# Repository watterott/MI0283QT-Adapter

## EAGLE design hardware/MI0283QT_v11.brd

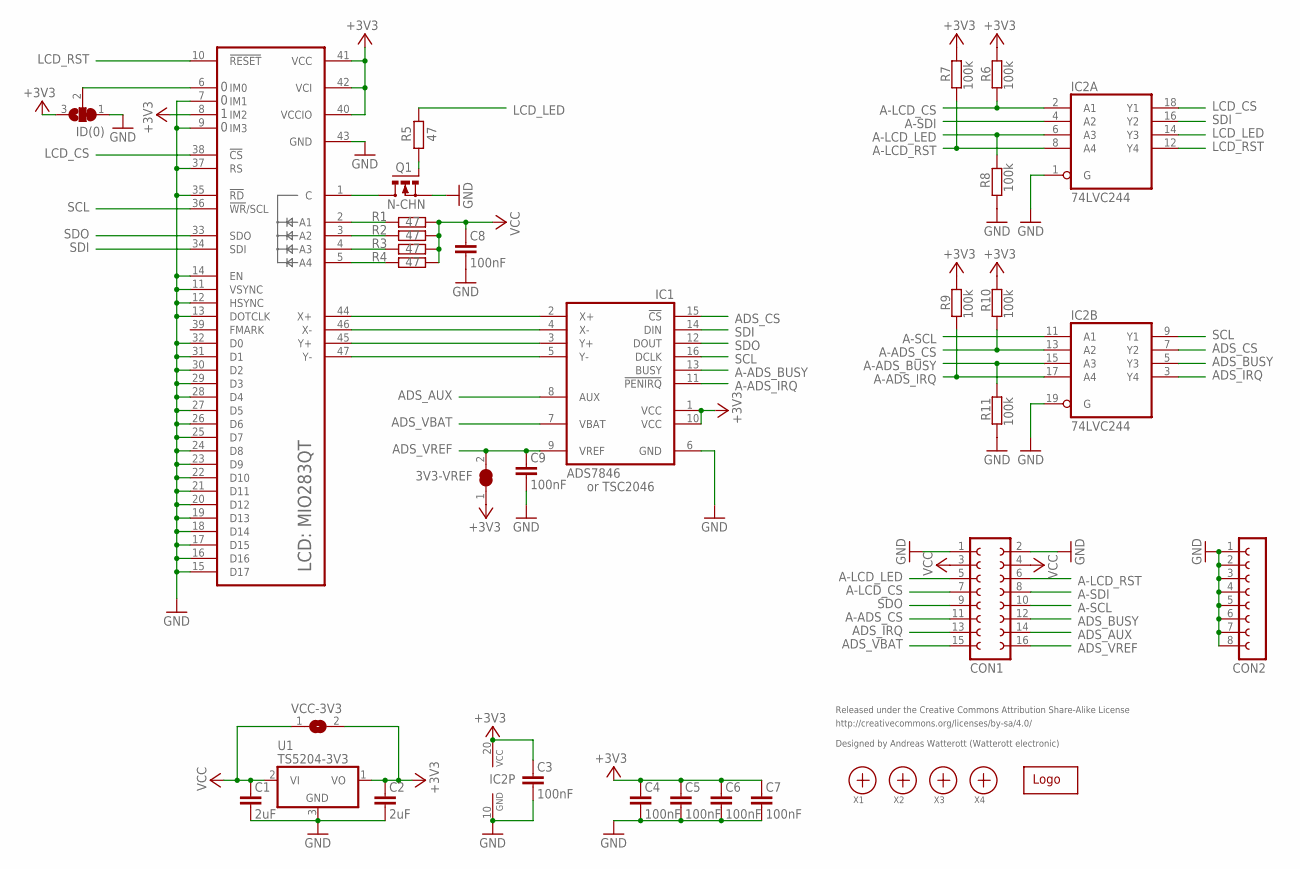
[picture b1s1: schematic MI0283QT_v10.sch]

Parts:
3V3-VREF: SJ
C1, C2: 2uF; C0805
C3, C4, C5, C6, C7, C8, C9: 100nF; C0603
CON1: FE08-2
CON2: FE08-1; FE08
IC1: ADS7846; SSOP16
IC2: 74LVC244; SO20W
ID(0): SJ2W; SJ_2
LCD: MI0283QT
Q1: N-CHN; MICRO3
R1, R2, R3, R4, R5: 47; R0603
R6, R7, R8, R9, R10, R11: 100k; R0603
U1: TS5204-3V3; SOT23
U$1: WE-LOGO
VCC-3V3: SJ
X1, X2, X3, X4: PASSER

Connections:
+3V3: 3V3-VREF.1, C2.1, C3.1, C4.1, C5.1, C6.1, C7.1, IC1.1 (VCC), IC1.10 (VCC), IC2.20 (VCC), ID(0).3, LCD.8 (IM2), LCD.40 (VCCIO), LCD.41 (VCC), LCD.42 (VCI), R6.2, R7.2, R9.2, R10.2, U1.1 (VO), VCC-3V3.2
A-ADS_BUSY: IC1.13 (BUSY), IC2.15 (A3), R11.1
A-ADS_CS: CON1.11, IC2.13 (A2), R10.1
A-ADS_IRQ: IC1.11 (!PENIRQ), IC2.17 (A4), R9.1
A-LCD_CS: CON1.7, IC2.2 (A1), R6.1
A-LCD_LED: CON1.5, IC2.6 (A3), R8.1
A-LCD_RST: CON1.6, IC2.8 (A4), R7.1
A-SCL: CON1.10, IC2.11 (A1)
A-SDI: CON1.8, IC2.4 (A2)
ADS_AUX: CON1.14, IC1.8 (AUX)
ADS_BUSY: CON1.12, IC2.5 (Y3)
ADS_CS: IC1.15 (!CS), IC2.7 (Y2)
ADS_IRQ: CON1.13, IC2.3 (Y4)
ADS_VBAT: CON1.15, IC1.7 (VBAT)
ADS_VREF: 3V3-VREF.2, C9.1, CON1.16, IC1.9 (VREF)
C: LCD.1 (C), Q1.3 (D)
GND: C1.2, C2.2, C3.2, C4.2, C5.2, C6.2, C7.2, C8.2, C9.2, CON1.1, CON1.2, CON2.1, CON2.2, CON2.3, CON2.4, CON2.5, CON2.6, CON2.7, CON2.8, IC1.6 (GND), IC2.1 (G), IC2.10 (GND), IC2.19 (G), ID(0).1, LCD.7 (IM1), LCD.9 (IM3), LCD.11 (VSYNC), LCD.12 (HSYNC), LCD.13 (DOTCLK), LCD.14 (EN), LCD.15 (D17), LCD.16 (D16), LCD.17 (D15), LCD.18 (D14), LCD.19 (D13), LCD.20 (D12), LCD.21 (D11), LCD.22 (D10), LCD.23 (D9), LCD.24 (D8), LCD.25 (D7), LCD.26 (D6), LCD.27 (D5), LCD.28 (D4), LCD.29 (D3), LCD.30 (D2), LCD.31 (D1), LCD.32 (D0), LCD.35 (!RD), LCD.37 (RS), LCD.43 (GND), Q1.2 (S), R8.2, R11.2, U1.3 (GND)
IM0: ID(0).2, LCD.6 (IM0)
LCD_CS: IC2.18 (Y1), LCD.38 (!CS)
LCD_LED: IC2.14 (Y3), R5.2
LCD_RST: IC2.12 (Y4), LCD.10 (!RESET)
LEDPWM: Q1.1 (G), R5.1
LED_A1: LCD.2 (A1), R1.1
LED_A2: LCD.3 (A2), R2.1
LED_A3: LCD.4 (A3), R3.1
LED_A4: LCD.5 (A4), R4.1
SCL: IC1.16 (DCLK), IC2.9 (Y1), LCD.36 (!WR!/SCL)
SDI: IC1.14 (DIN), IC2.16 (Y2), LCD.34 (SDI)
SDO: CON1.9, IC1.12 (DOUT), LCD.33 (SDO)
VCC: C1.1, C8.1, CON1.3, CON1.4, R1.2, R2.2, R3.2, R4.2, U1.2 (VI), VCC-3V3.1
X+: IC1.2 (X+), LCD.44 (X+)
X-: IC1.4 (X-), LCD.46 (X-)
Y+: IC1.3 (Y+), LCD.45 (Y+)
Y-: IC1.5 (Y-), LCD.47 (Y-)

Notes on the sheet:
Released under the Creative Commons Attribution Share-Alike License
http://creativecommons.org/licenses/by-sa/4.0/
Designed by Andreas Watterott (Watterott electronic)
or TSC2046

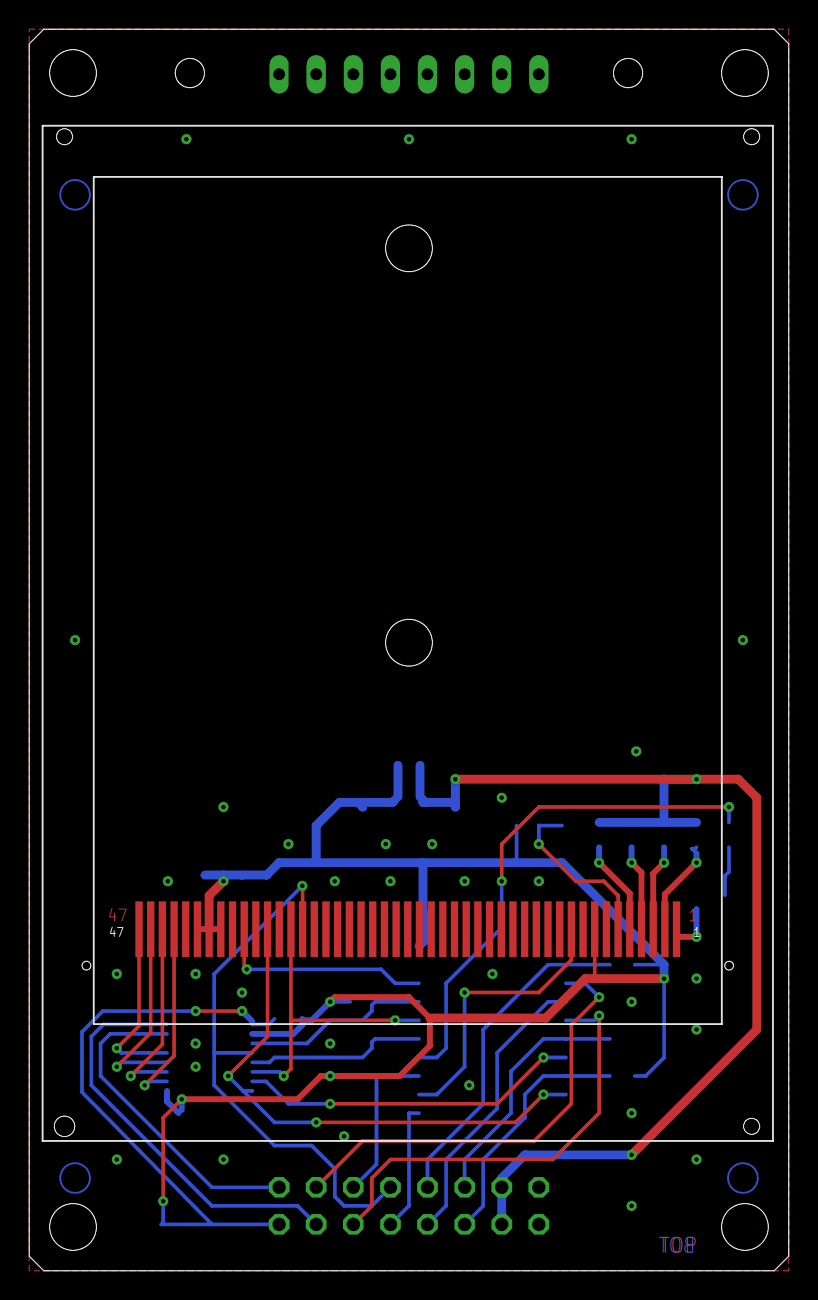
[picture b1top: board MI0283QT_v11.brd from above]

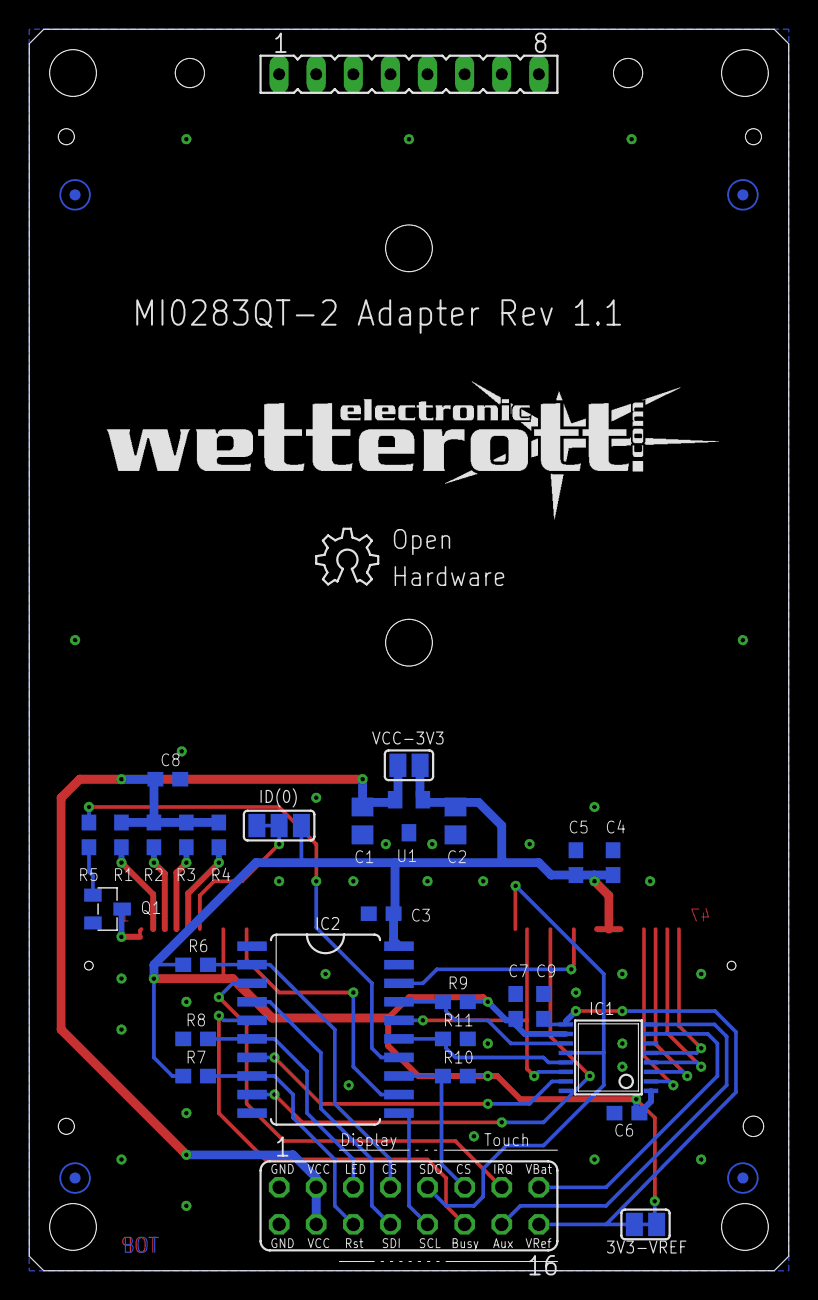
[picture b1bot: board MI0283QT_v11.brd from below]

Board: 2 copper layers, 52.0 x 85.0 mm, 36 parts (35 on the bottom side), 34 nets.

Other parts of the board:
LOGO1: OSHW_LOGO_6MILX0150-NT; OSHW_6X150_NOTEXT
